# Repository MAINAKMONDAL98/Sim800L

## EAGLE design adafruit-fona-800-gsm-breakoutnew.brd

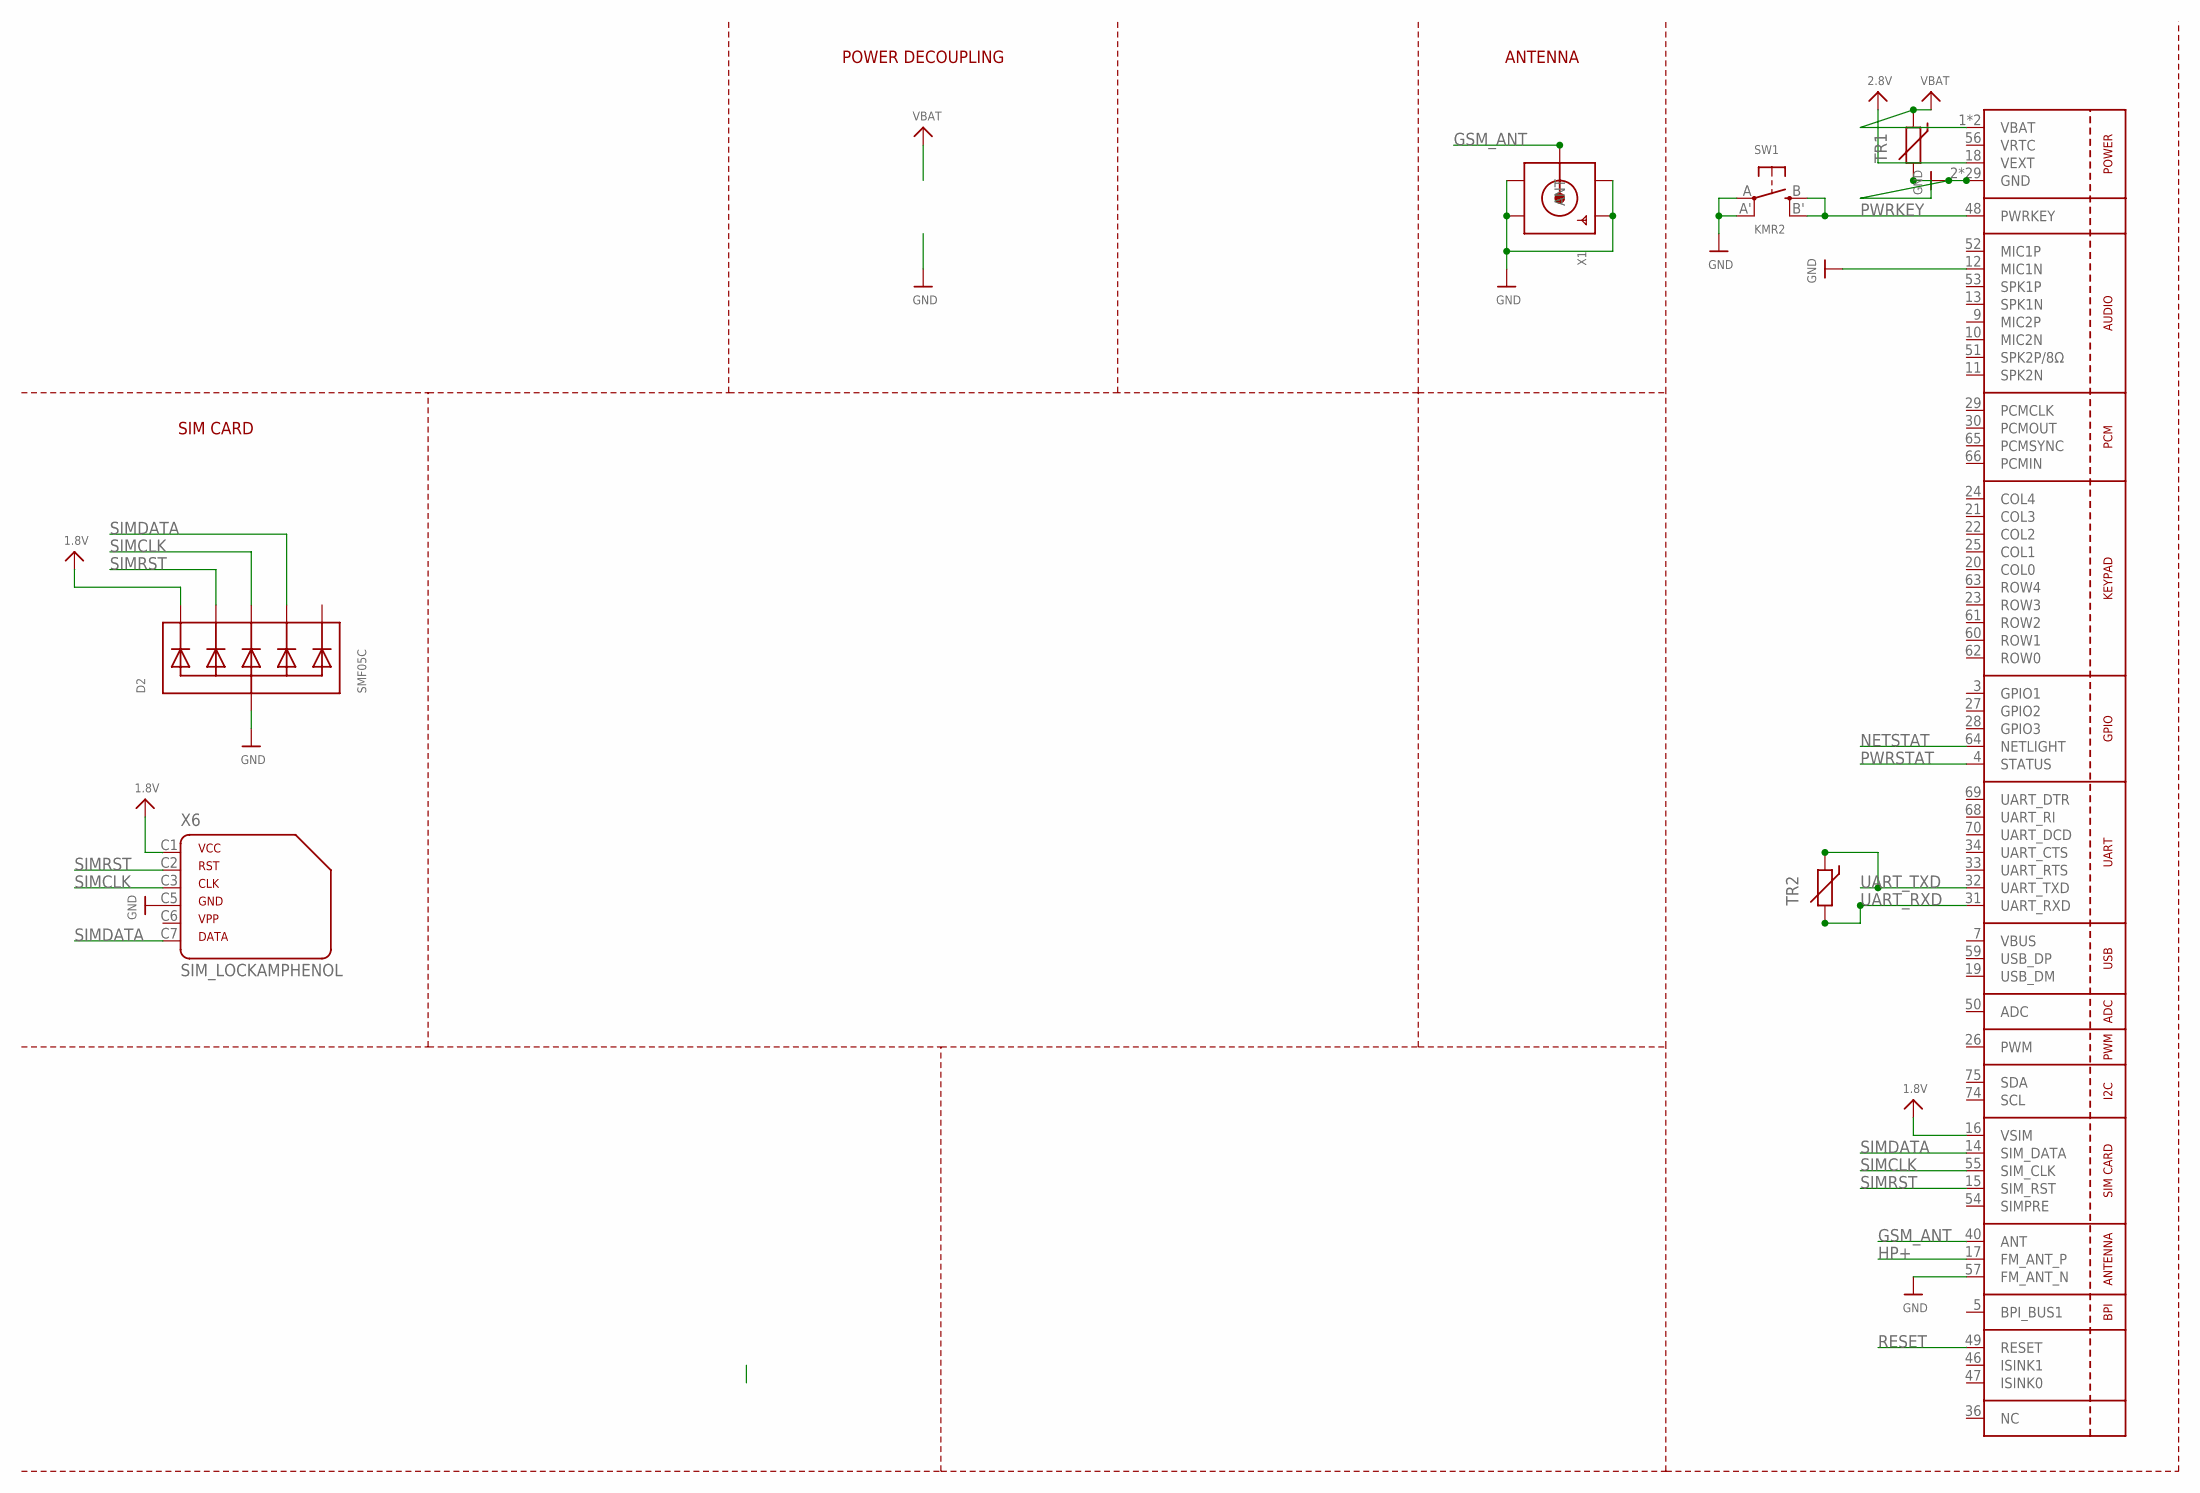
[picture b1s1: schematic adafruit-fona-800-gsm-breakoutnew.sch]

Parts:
D2: SMF05C; SOT363
SW1: KMR2; BTN_KMR2_4.6X2.8
TR1, TR2: THERMISTOR_R-5; R-5
U1: ss; SIM800L
X1: SMACONNECTOR_EDGE_UFL; SMA_EDGELAUNCH_UFL
X6: SIM_LOCKAMPHENOL; C707_10M006_512_2

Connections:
1.8V: D2.1 (C1), U1.16 (VSIM), X6.C1 (1)
2.8V: U1.18 (VEXT)
GND: D2.2 (A), SW1.A, SW1.A' (P1), TR1.2, U1.2 (GND), U1.6 (GND), U1.8 (GND), U1.12 (MIC1N), U1.35 (GND), U1.37 (GND), U1.38 (GND), U1.39 (GND), U1.41 (GND), U1.43 (GND), U1.44 (GND), U1.45 (GND), U1.57 (FM_ANT_N), U1.58 (GND), U1.67 (GND), U1.71 (GND), U1.72 (GND), U1.73 (GND), U1.76 (GND), U1.77 (GND), U1.78 (GND), U1.79 (GND), U1.80 (GND), U1.81 (GND), U1.82 (GND), U1.83 (GND), U1.84 (GND), U1.85 (GND), U1.86 (GND), U1.87 (GND), U1.88 (GND), X1.GND@1 (GND1), X1.GND@2 (GND2), X1.GND@3 (GND3), X1.GND@4 (GND4), X6.C5 (4)
GSM_ANT: U1.40 (ANT), X1.P (ANT)
HP+: U1.17 (FM_ANT_P)
NETSTAT: U1.64 (NETLIGHT)
PWRKEY: SW1.B (S), SW1.B' (S1), U1.48 (PWRKEY)
PWRSTAT: U1.4 (STATUS)
RESET: U1.49 (RESET)
SIMCLK: D2.4 (C3), U1.55 (SIM_CLK), X6.C3 (3)
SIMDATA: D2.5 (C4), U1.14 (SIM_DATA), X6.C7 (6)
SIMRST: D2.3 (C2), U1.15 (SIM_RST), X6.C2 (2)
UART_RXD: TR2.2, U1.31 (UART_RXD)
UART_TXD: TR2.1, U1.32 (UART_TXD)
VBAT: TR1.1, U1.1 (VBAT), U1.42 (VBAT)
VBUS: U1.7 (VBUS)
VRTC: U1.56 (VRTC)

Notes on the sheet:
ANTENNA
POWER DECOUPLING
SIM CARD

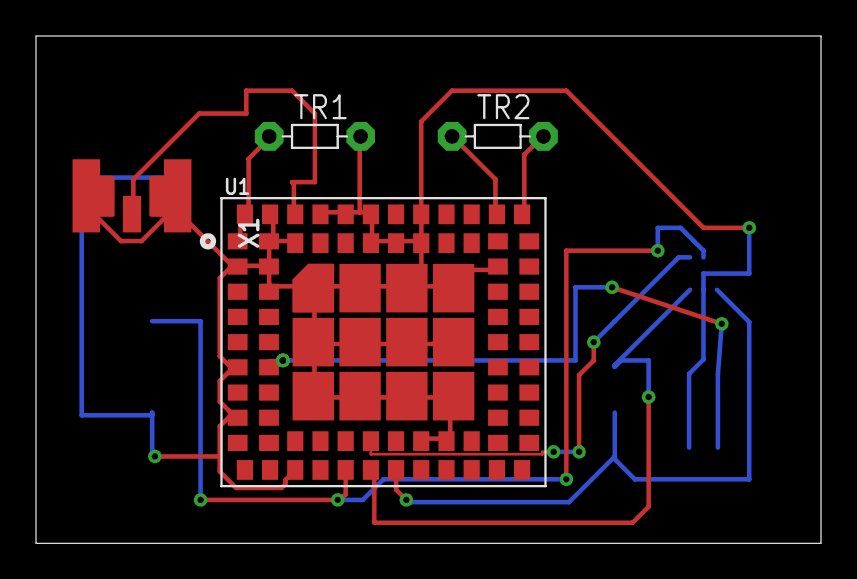
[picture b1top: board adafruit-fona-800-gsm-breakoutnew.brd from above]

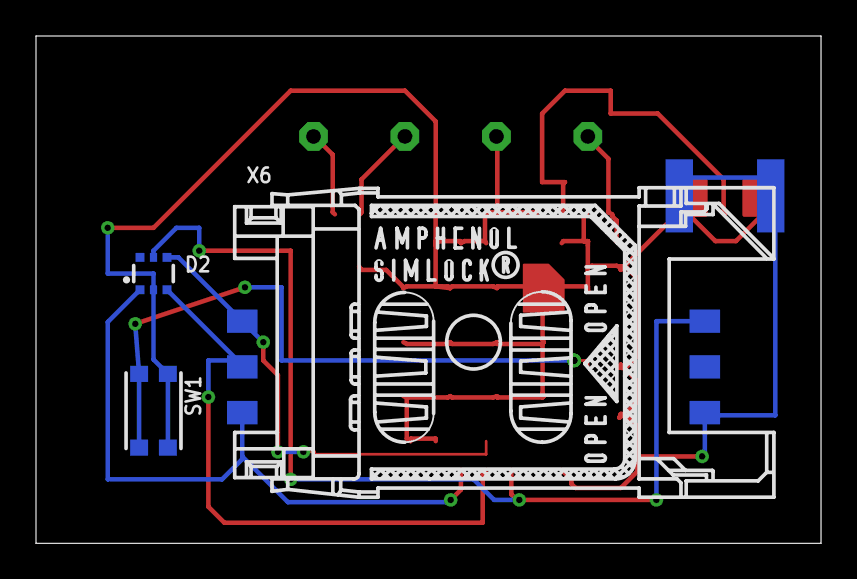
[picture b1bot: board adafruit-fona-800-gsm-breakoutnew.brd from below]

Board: 2 copper layers, 43.6 x 28.2 mm, 7 parts (3 on the bottom side), 10 nets.

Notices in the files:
parts and their libraries:
microbuilder: This work is placed in the public domain, and may be freely used for commercial and non-commercial work with the following conditions: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
